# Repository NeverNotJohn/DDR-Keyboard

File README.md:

# DDR-Keyboard
Keyboard for them DDR addicts

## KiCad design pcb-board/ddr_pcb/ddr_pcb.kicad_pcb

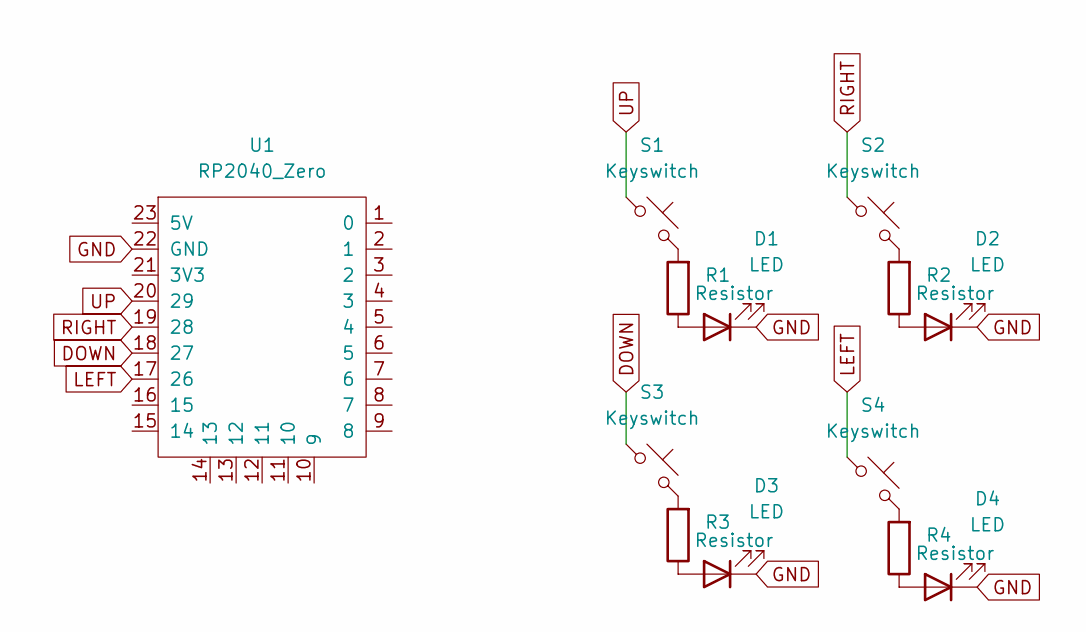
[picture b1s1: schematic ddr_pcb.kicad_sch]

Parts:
D1, D2, D3, D4: LED; LED_D1.8mm_W1.8mm_H2.4mm_Horizontal_O1.27mm_Z1.6mm
R1, R2, R3, R4: Resistor; R_Axial_DIN0207_L6.3mm_D2.5mm_P10.16mm_Horizontal
S1, S2, S3, S4: Keyswitch; Choc_20x20mm
U1: RP2040_Zero

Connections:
DOWN: S3.1, U1.18 (27)
GND: D1.1 (K), D2.1 (K), D3.1 (K), D4.1 (K), U1.22 (GND)
LEFT: S4.1, U1.17 (26)
unnamed: D1.2 (A), R1.1
unnamed: D2.2 (A), R2.1
unnamed: D3.2 (A), R3.1
unnamed: D4.2 (A), R4.1
unnamed: R1.2, S1.2
unnamed: R2.2, S2.2
unnamed: R3.2, S3.2
unnamed: R4.2, S4.2
RIGHT: S2.1, U1.19 (28)
UP: S1.1, U1.20 (29)

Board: 2 copper layers, 13 parts (5 on the bottom side), 13 nets, no tracks yet.

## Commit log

2024-06-21 started pcb design
2024-06-25 yay update
2024-06-26 like my 3rd pcb design
2024-07-02 starting code
2024-07-02 Initial User Config.
